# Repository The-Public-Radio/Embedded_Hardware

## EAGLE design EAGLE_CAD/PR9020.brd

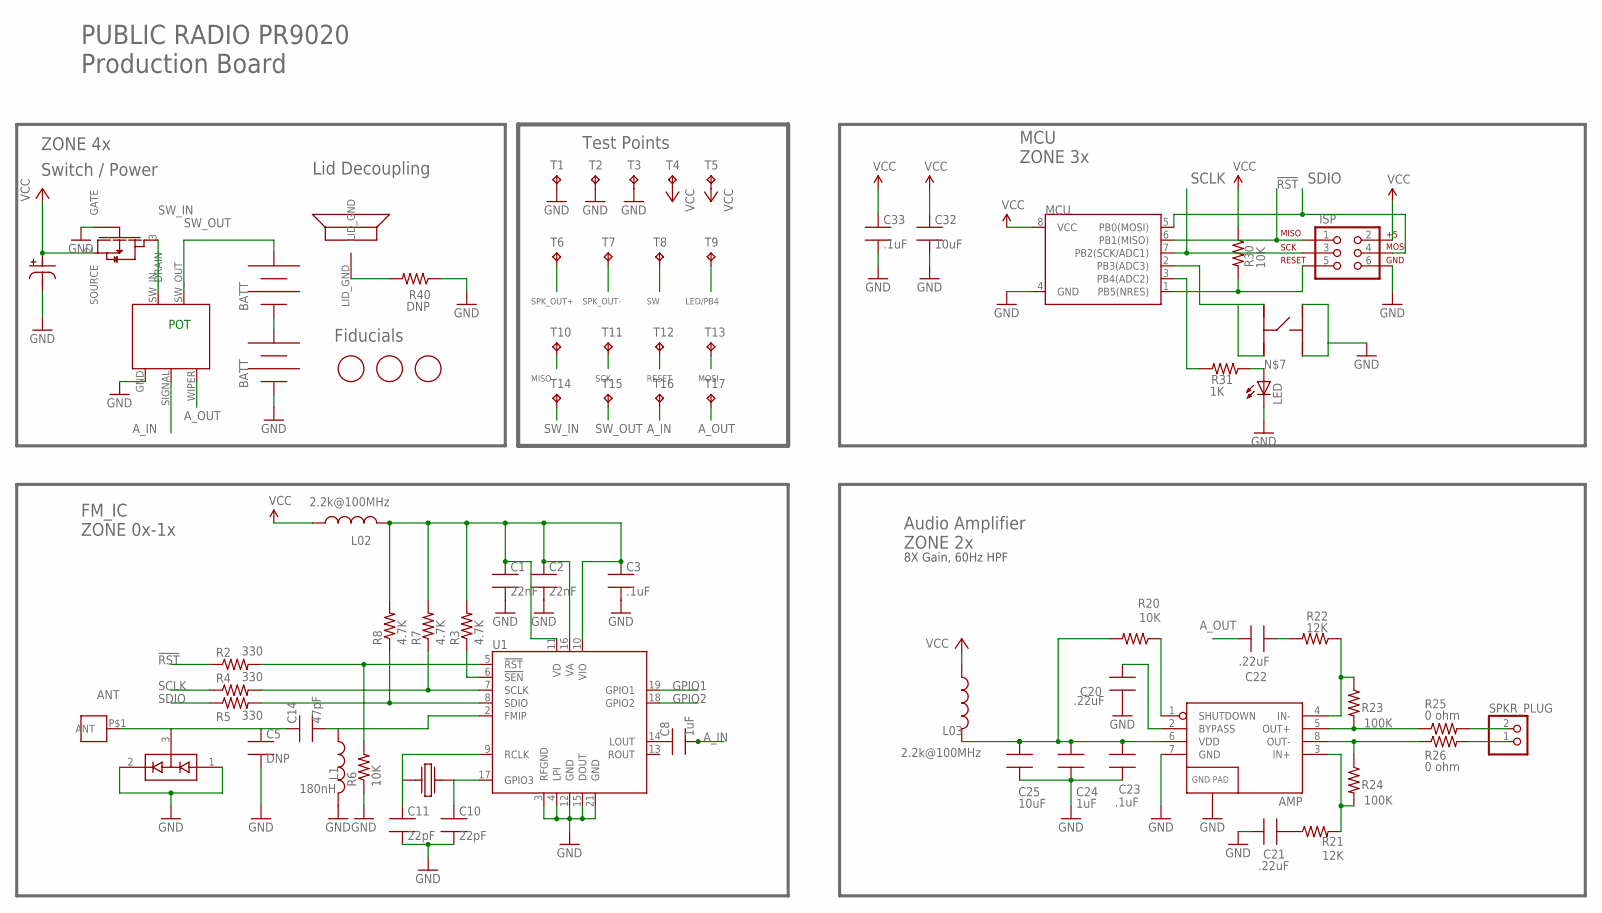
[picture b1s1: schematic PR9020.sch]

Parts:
AMP: TPA6203A1; 8-MSOP
ANT_MOUNT: DNP; M3_BOLT_HOLE
C1, C2: 22nF; 0603_CPL; VOLTAGE 16V; MFG_PN CL10B223KB8NNNC
C3, C23, C33: .1uF; 0603_CPL; VOLTAGE 16V; MFG_PN CL10B104KB8SFNC
C5: DNP; 0603_CPL; VOLTAGE 50V; MFG_PN DNP
C8, C24: 1uF; 0603_CPL; VOLTAGE 10V; MFG_PN CL10B105KP8NNNC
C10, C11: 22pF; 0603_CPL; VOLTAGE 50V; MFG_PN C1608C0G1H220J080AA
C14: 47pF; 0603_CPL; VOLTAGE 50V; MFG_PN CL10C470JB8NCNC
C20, C21, C22: .22uF; 0603_CPL; VOLTAGE 16V; MFG_PN C1608X7R1C224K080AC
C25, C32: 10uF; 0603_CPL; VOLTAGE 6.3V; MFG_PN CL10A106MQ8NNNC
C40: 220uF; NICHICON_UD_63; VOLTAGE 16V
D1: BAV99; SOT23_CPL; MFG_PN BAV99,215
FET1: AO3435; SOT23_CPL; MFG_PN AO3435
ISP: AVR_SPI_PRG_6NS; 2X3-NS
JP5, JP6: BK-92_MPD_AA_BATT_CLIP; BK92_AA_BATT; MFG_PN 2 of BK92 - supplied by CL Labs
L1: 180nH; 0805_ADAFRUIT; MFG_PN AISC-0805-R18J-T
L02, L03: 2.2k@100MHz; 0603_CPL; MFG_PN HZ0603A222R-10
LED: LEDCHIPLED_0805; CHIPLED_0805; MFG_PN LY R976-PS-36
MARK1, MARK2, MARK3: FIDUCIAL; FIDUCIAL_1MM
MCU: ATTINY45TINY45-20-SMT; 8-SOIC
R1: RV170SF_TAIWANA_POT_SW; RV170SF_SW_POT; MFG_PN RV170SF-43-20F-A10K - supplied by CL La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
R2, R4, R5: 330; 0603_CPL; MFG_PN MCR03ERTJ331
R3, R7, R8: 4.7K; 0603_CPL; MFG_PN ERJ-3EKF4701V
R6, R20, R30: 10K; 0603_CPL; MFG_PN ERJ-3GEYJ103V
R21, R22: 12K; 0603_CPL; MFG_PN RC0603FR-0712KL
R23, R24: 100K; 0603_CPL; MFG_PN ERJ-3EKF1003V
R25, R26: 0 ohm; 0805_ADAFRUIT; MFG_PN ERJ-6GEY0R00V
R31: 1K; 0603_CPL; MFG_PN ERJ-3EKF1001V
R40: DNP; 0603_CPL; MFG_PN ERJ-3GEY0R00V
SPKR_PLACE: DNP; PR2023_SPKR_PLACE
SPKR_PLUG: JST_2PIN-SMT-RA; JST-B2B-PH-SM4-TB
SW1: C&K_PTS645; C&K_PTS645_SMT
T1, T2, T3, T4, T5, T6, T7, T8, T9, T10, T11, T12, T13, T14, T15, T16, T17: TPTP20R; TP20R
U1: SI4702-C19-GMR; SI470X_20_QFN; MFG_PN Si4702 C19 GM - supplied by CL Labs
X1: ABS25XTAL; 4-SOJ

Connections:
3.3V: C1.1, C2.1, C3.1, L02.2, R3.2, R7.2, R8.2, U1.10 (VIO), U1.11 (VD), U1.16 (VA)
!RST: ISP.1, MCU.6 (PB1(MISO)), R2.1, T10.TP
!RST-L: R2.2, R6.2, U1.5 (!RST)
!SEN-L: R3.1, U1.6 (!SEN)
ANT: ANT_MOUNT.P$1, C5.1, C14.1, D1.3 (COM)
A_IN: C8.2, R1.SIGNAL, T16.TP
A_OUT: C22.2, R1.WIPER, T17.TP
GND: AMP.7 (GND), AMP.9 (GND), C1.2, C2.2, C3.2, C5.2, C10.2, C11.2, C20.1, C21.1, C23.2, C24.2, C25.2, C32.2, C33.2, C40.P$2, D1.1 (A1), D1.2 (C2), FET1.1 (GATE), ISP.6, JP6.NEG, JP6.NEG@2 (NEG), L1.2, LED.C, MCU.4 (GND), R1.GND, R6.1, R40.1, SW1.P$1, SW1.P$2, T1.TP, T2.TP, T3.TP, U1.3 (RFGND), U1.4 (LPI), U1.12 (GND), U1.15 (DOUT), U1.21 (GND)
GPIO1: U1.19 (GPIO1)
GPIO2: U1.18 (GPIO2)
LED/PB4: MCU.3 (PB4(ADC2)), R31.2, T9.TP
unnamed: C11.1, U1.9 (RCLK), X1.P$1
unnamed: AMP.6 (VDD), C23.1, C24.1, C25.1, L03.2, R20.2
unnamed: C22.1, R22.2
unnamed: AMP.5 (OUT+), R23.2, R25.1
unnamed: AMP.3 (IN+), R21.2, R24.2
unnamed: LED.A, R31.1
unnamed: R40.2, SPKR_PLACE.LID_GND
unnamed: C8.1, U1.14 (LOUT)
unnamed: C10.1, U1.17 (GPIO3), X1.P$4
unnamed: AMP.8 (OUT-), R24.1, R26.1
unnamed: AMP.2 (BYPASS), C20.2
unnamed: JP5.NEG, JP5.NEG@2 (NEG), JP6.POS, JP6.POS@2 (POS)
unnamed: AMP.4 (IN-), R22.1, R23.1
unnamed: C14.2, L1.1, U1.2 (FMIP)
unnamed: AMP.1 (SHUTDOWN), R20.1
unnamed: C21.2, R21.1
RESET: ISP.5, MCU.1 (PB5(NRES)), R30.2, T12.TP
SCLK: ISP.3, MCU.7 (PB2(SCK/ADC1)), R4.1, T11.TP
SCLK-L: R4.2, R7.1, U1.7 (SCLK)
SDIO: ISP.4, MCU.5 (PB0(MOSI)), R5.1, T13.TP
SDIO-L: R5.2, R8.1, U1.8 (SDIO)
SPK_OUT+: R25.2, SPKR_PLUG.2 (1), T6.TP
SPK_OUT-: R26.2, SPKR_PLUG.1 (2), T7.TP
SW: MCU.2 (PB3(ADC3)), SW1.P$3, SW1.P$4, T8.TP
SW_IN: FET1.3 (DRAIN), R1.SW_IN, T14.TP
SW_OUT: JP5.POS, JP5.POS@2 (POS), R1.SW_OUT, T15.TP
VCC: C32.1, C33.1, C40.P$1, FET1.2 (SOURCE), ISP.2, L02.1, L03.1, MCU.8 (VCC), R30.1, T4.TP, T5.TP

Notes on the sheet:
POT
FM_IC ZONE 0x-1x
Switch / Power
Lid Decoupling
Audio Amplifier ZONE 2x
MCU ZONE 3x
PUBLIC RADIO PR9020 Production Board
Fiducials
Test Points
MISO
SCK
RESET
MOSI
8X Gain, 60Hz HPF
ZONE 4x

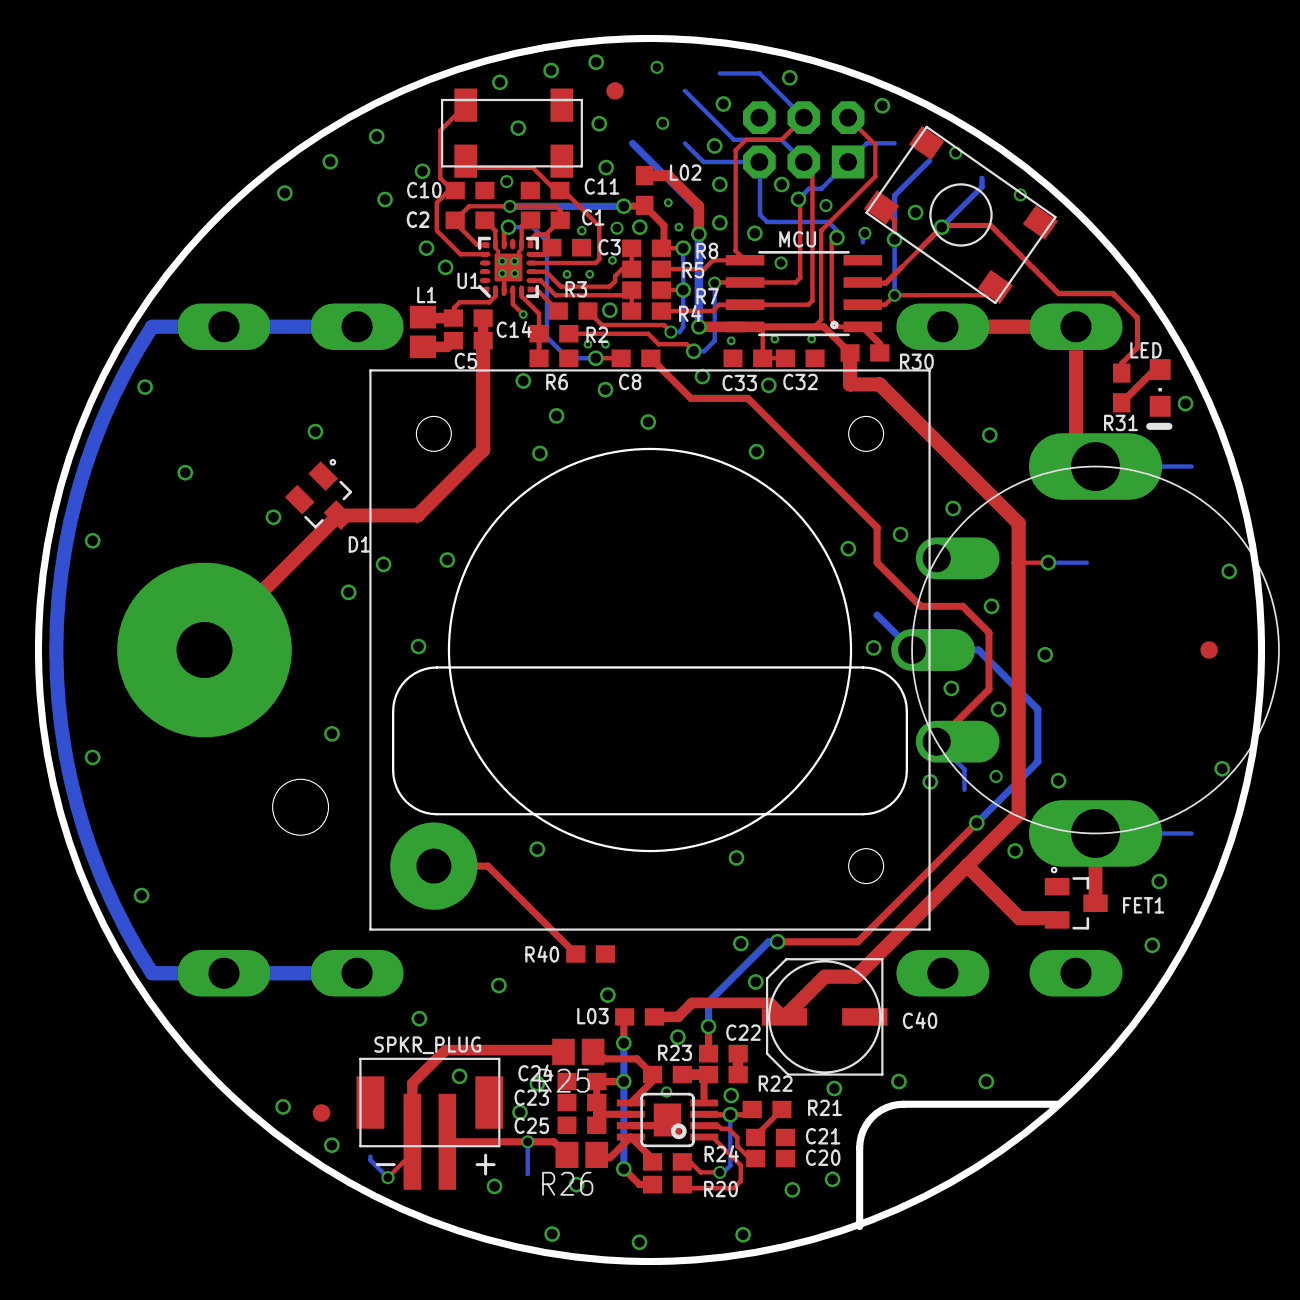
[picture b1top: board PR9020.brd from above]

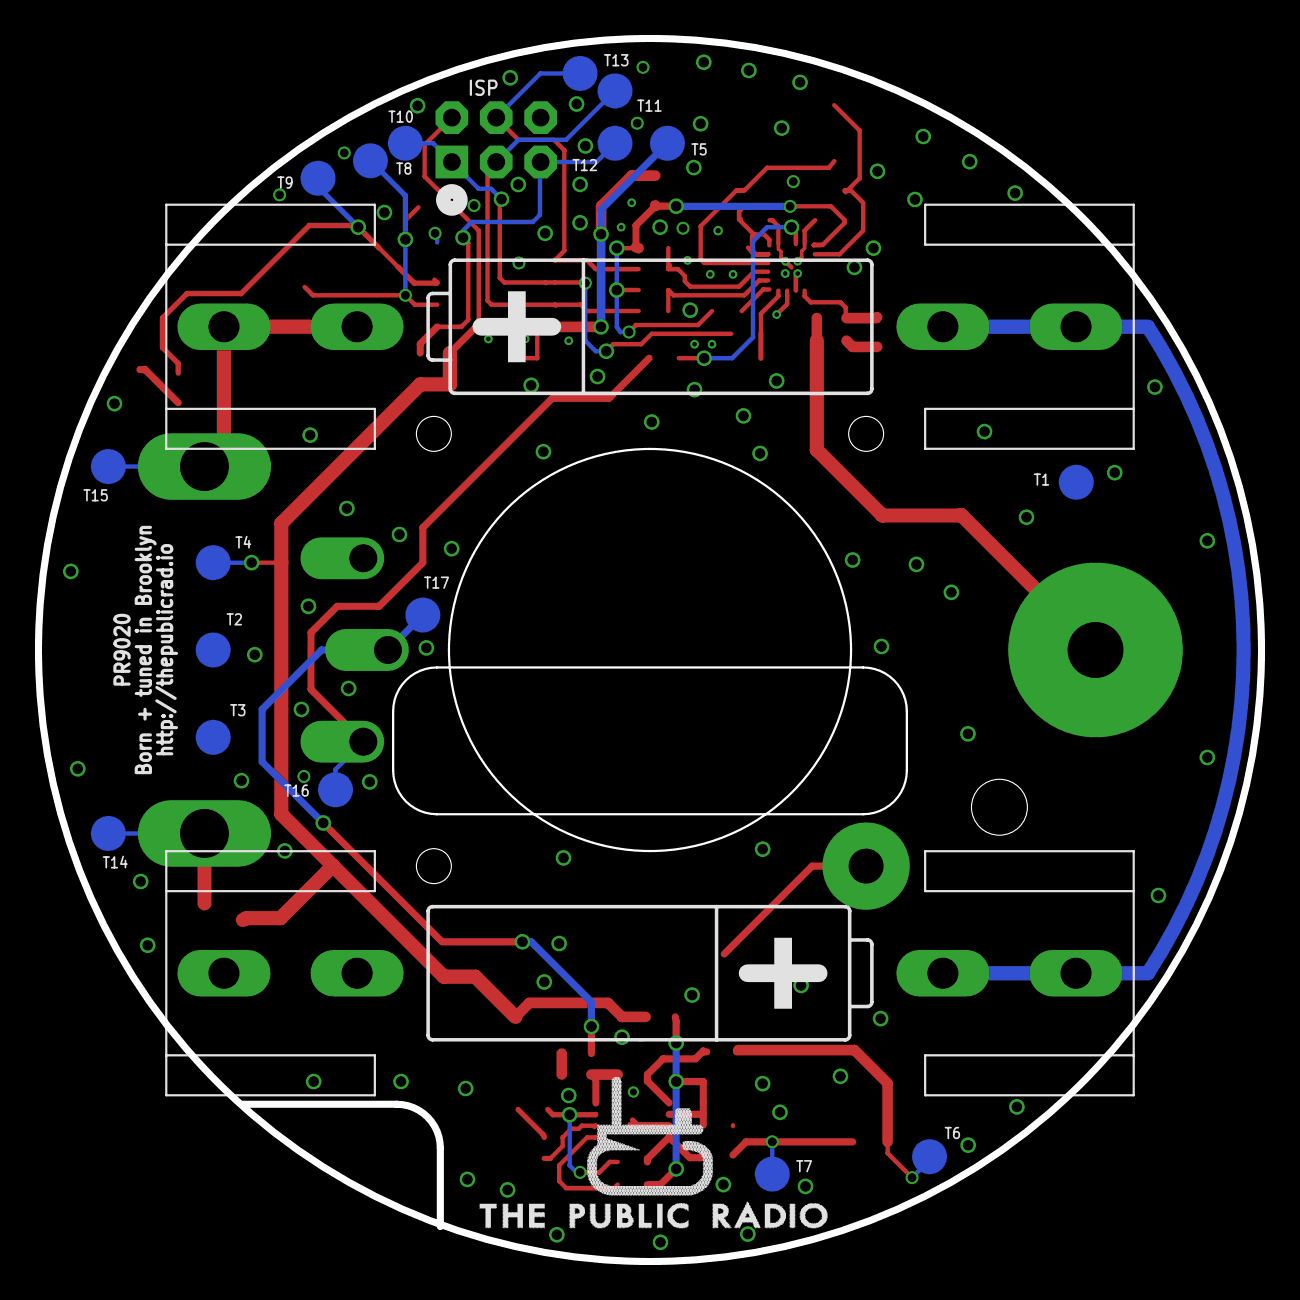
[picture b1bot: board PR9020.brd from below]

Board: 2 copper layers, 70.0 x 70.0 mm, 73 parts (21 on the bottom side), 36 nets.

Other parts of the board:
U$1: PR_LOGO

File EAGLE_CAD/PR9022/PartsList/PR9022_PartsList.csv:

Partlist

Exported from PR9022.brd at 9/28/15 9:47 PM

EAGLE Version 6.6.0 Copyright (c) 1988-2014 CadSoft

Assembly variant: 

Part       Value          Package           Library          Position (mm)         Orientation

AMP                       8-MSOP            PR_Parts_Library (34.1 10.2)           R0
ANT_MOUNT  DNP            PEM_M3            PR_Parts_Library (9.5 35)              R0
C1         22nF           0603_CPL          PR_Parts_Library (29.01 59.6)          R180
C2         22nF           0603_CPL          PR_Parts_Library (24.7 59.6)           R0
C3         .1uF           0603_CPL          PR_Parts_Library (30.24 58.03)         R0
C8         1uF            0603_CPL          PR_Parts_Library (34.2 51.7)           R0
C10        22pF           0603_CPL          PR_Parts_Library (24.7 61.3)           R0
C11        22pF           0603_CPL          PR_Parts_Library (29 61.3)             R180
C14        47pF           0603_CPL          PR_Parts_Library (24.7 54)             R180
C20        .22uF          0603_CPL          PR_Parts_Library (31.8 4)              R0
C21        .22uF          0603_CPL          PR_Parts_Library (35.5 2.2)            R0
C22        .22uF          0603_CPL          PR_Parts_Library (38.5 7)              R90
C23        .1uF           0603_CPL          PR_Parts_Library (34.5 15.1)           R90
C24        1uF            0603_CPL          PR_Parts_Library (36.5 15.1)           R90
C25        10uF           0603_CPL          PR_Parts_Library (32.5 15.1)           R90
C32        10uF           0603_CPL          PR_Parts_Library (42 52.3)             R270
C33        .1uF           0603_CPL          PR_Parts_Library (40.2 52.3)           R270
C40        220uF          NICHICON_UD_63    PR_Parts_Library (45.7 12.2)           R180
D1                        SOT23_CPL         PR_Parts_Library (16.4 43.5)           R315
FET1                      SOT23_CPL         PR_Parts_Library (59.4 20.5)           R0
ISP                       2X3-NS            PR_Parts_Library (43.8 64.2)           MR0
JP5                       BK92_AA_BATT      PR_Parts_Library (35 53.5)             MR180
JP6                       BK92_AA_BATT      PR_Parts_Library (35 16.5)             MR0
L1         180nH          0805_ADAFRUIT     PR_Parts_Library (22 53.2)             R270
L02        2.2k@100MHz    0603_CPL          PR_Parts_Library (34.7 61.3)           R270
L03        2.2k@100MHz    0603_CPL          PR_Parts_Library (40 11.8)             R90
LED                       CHIPLED_0805      adafruit         (64.2 50)             R180
MARK1                     FIDUCIAL_1MM      PR_Parts_Library (16.2 8.5)            R0
MARK2                     FIDUCIAL_1MM      PR_Parts_Library (33 67)               R0
MARK3                     FIDUCIAL_1MM      PR_Parts_Library (67 35)               R0
MCU                       8-SOIC            PR_Parts_Library (43.7 56.4)           R90
R1                        RV170SF_SW_POT    PR_Parts_Library (60.5 35)             R270
R2         330            0603_CPL          PR_Parts_Library (29.5 53.1)           R180
R3         4.7K           0603_CPL          PR_Parts_Library (30.6 54.4)           R0
R4         330            0603_CPL          PR_Parts_Library (34.8 54.4)           R180
R5         330            0603_CPL          PR_Parts_Library (34.8 56.8)           R180
R6         10K            0603_CPL          PR_Parts_Library (29.5 51.7)           R180
R7         4.7K           0603_CPL          PR_Parts_Library (34.8 55.6)           R0
R8         4.7K           0603_CPL          PR_Parts_Library (34.8 58)             R0
R20        10K            0603_CPL          PR_Parts_Library (29.9 10.2)           R90
R21        12K            0603_CPL          PR_Parts_Library (35.5 4)              R180
R22        12K            0603_CPL          PR_Parts_Library (36.7 7)              R270
R23        100K           0603_CPL          PR_Parts_Library (36.7 10.2)           R90
R24        100K           0603_CPL          PR_Parts_Library (31.7 10.2)           R270
R25        0 ohm          0805_ADAFRUIT     PR_Parts_Library (38.6 15.1)           R90
R26        0 ohm          0805_ADAFRUIT     PR_Parts_Library (30.4 15.1)           R90
R30        10K            0603_CPL          PR_Parts_Library (45.4 53)             R0
R31        1K             0603_CPL          PR_Parts_Library (62 50)               R90
R40        DNP            0603_CPL          PR_Parts_Library (24.2 15.3)           R90
SPKR_PLACE DNP            PR2024_SPKR_PLACE PR_Parts_Library (35 35)               R0
SW1                       C&K_PTS645_SMT    PR_Parts_Library (52.8 59.9)           R325
T1                        TP20R             PR_Parts_Library (10.6 44.6)           MR0
T2                        TP20R             PR_Parts_Library (60 35)               MR0
T3                        TP20R             PR_Parts_Library (60 30)               MR0
T4                        TP20R             PR_Parts_Library (60 40)               MR0
T5                        TP20R             PR_Parts_Library (34 64)               MR0
T6                        TP20R             PR_Parts_Library (37 21)               MR0
T7                        TP20R             PR_Parts_Library (32 21)               MR0
T8                        TP20R             PR_Parts_Library (51 63)               MR0
T9                        TP20R             PR_Parts_Library (54 62)               MR0
T10                       TP20R             PR_Parts_Library (49 64)               MR0
T11                       TP20R             PR_Parts_Library (37 67)               MR0
T12                       TP20R             PR_Parts_Library (37 64)               MR0
T13                       TP20R             PR_Parts_Library (39 68)               MR0
T14                       TP20R             PR_Parts_Library (66 24.5)             MR0
T15                       TP20R             PR_Parts_Library (66 45.5)             MR0
T16                       TP20R             PR_Parts_Library (53 27)               MR0
T17                       TP20R             PR_Parts_Library (48 37)               MR0
U1                        SI470X_20_QFN     PR_Parts_Library (26.9 56.9)           R90
X1                        4-SOJ             PR_Parts_Library (27.2 64.58)          R0

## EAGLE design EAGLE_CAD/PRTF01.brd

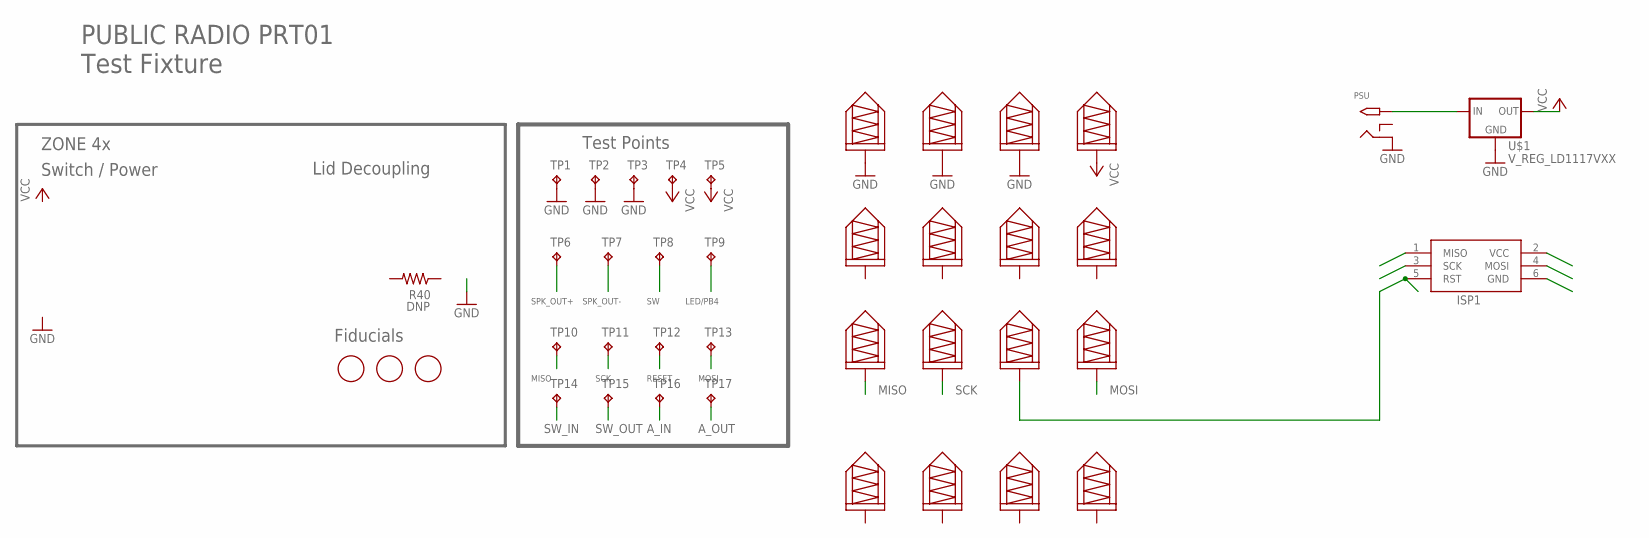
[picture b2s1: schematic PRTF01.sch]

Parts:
ISP1: AVRISP-6; AVRISP
MARK1, MARK2, MARK3: FIDUCIAL; FIDUCIAL_1MM
P1, P2, P3, P4, P6, P8, P9, P10, P11, P12, P13, P14, P15, P16, P17: 0908MILL_MAX_SPRINGPIN
PSU: 2.1MMJACKTHM; PJ-102A
R40: DNP; 0603_CPL; MFG_PN ERJ-3GEY0R00V
TP1, TP2, TP3, TP4, TP5, TP6, TP7, TP8, TP9, TP10, TP11, TP12, TP13, TP14, TP15, TP16, TP17: TPTP20R; TP20R
U$1: V_REG_LD1117VXX; 78XXL
U$P7: 0908MILL_MAX_SPRINGPIN

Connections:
!RST: TP10.TP
A_IN: TP16.TP
A_OUT: TP17.TP
GND: P1.P$1, P2.P$1, P3.P$1, PSU.RING, TP1.TP, TP2.TP, TP3.TP, U$1.IN (GND)
LED/PB4: TP9.TP
MISO: ISP1.1 (MISO), P10.P$1
MOSI: ISP1.4 (MOSI), P13.P$1
unnamed: PSU.TIP, U$1.OUT (IN)
RESET: ISP1.5 (RST), P12.P$1, TP12.TP
SCK: ISP1.3 (SCK), P11.P$1
SCLK: TP11.TP
SDIO: TP13.TP
SPK_OUT+: TP6.TP
SPK_OUT-: TP7.TP
SW: TP8.TP
SW_IN: TP14.TP
SW_OUT: TP15.TP
VCC: P4.P$1, TP4.TP, TP5.TP, U$1.GND (OUT)

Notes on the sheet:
Switch / Power
Lid Decoupling
PUBLIC RADIO PRT01 Test Fixture
Fiducials
Test Points
MISO
SCK
RESET
MOSI
ZONE 4x

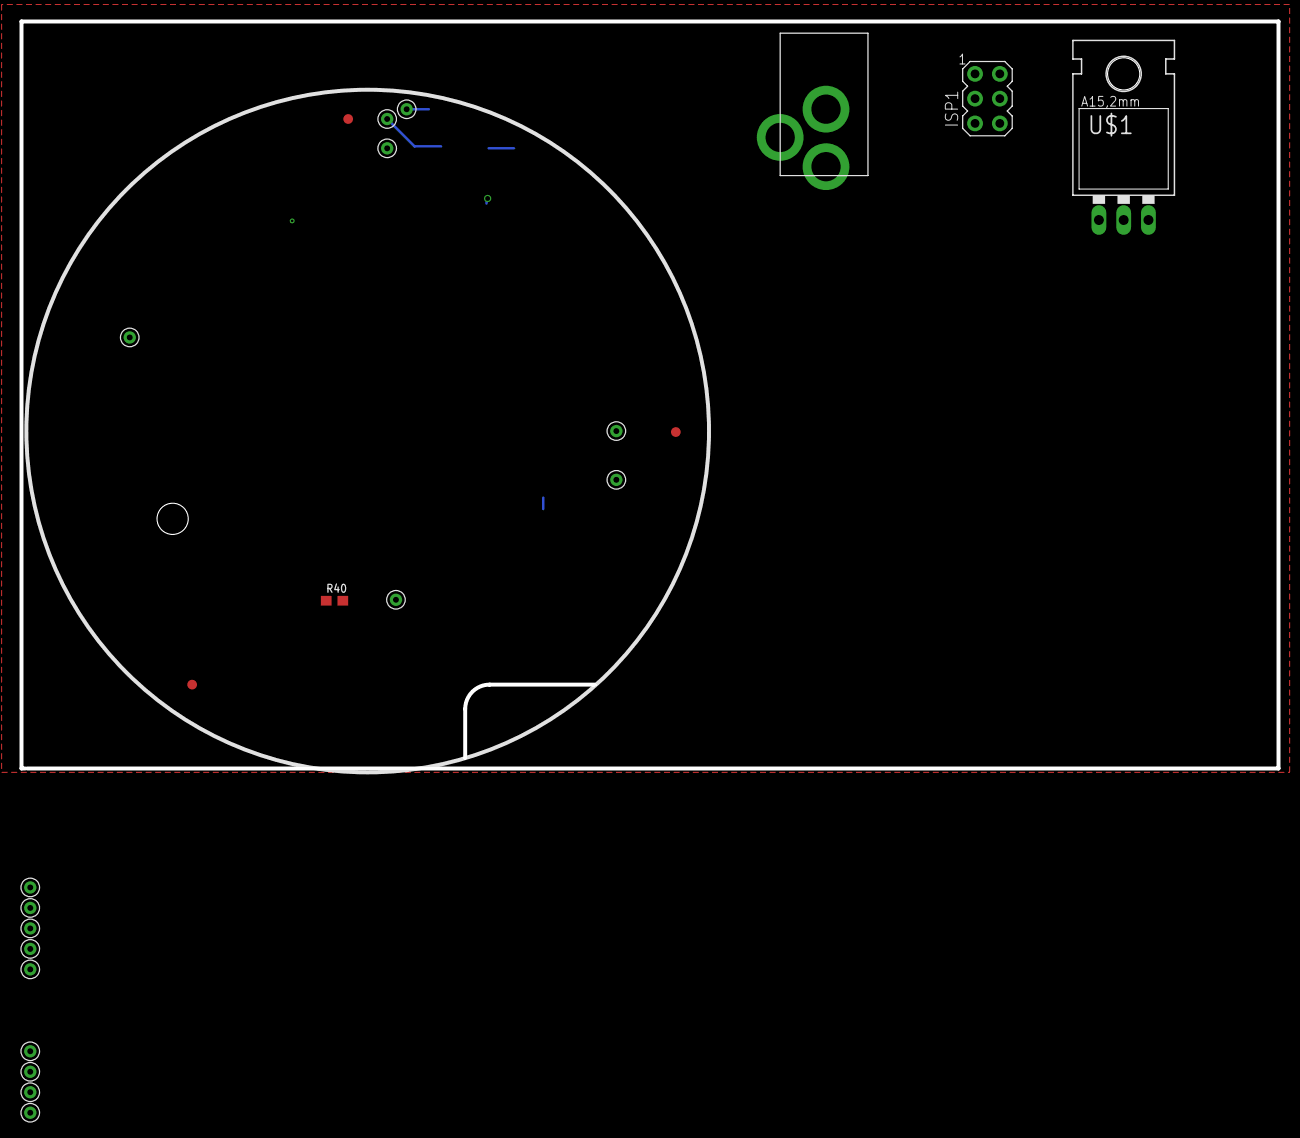
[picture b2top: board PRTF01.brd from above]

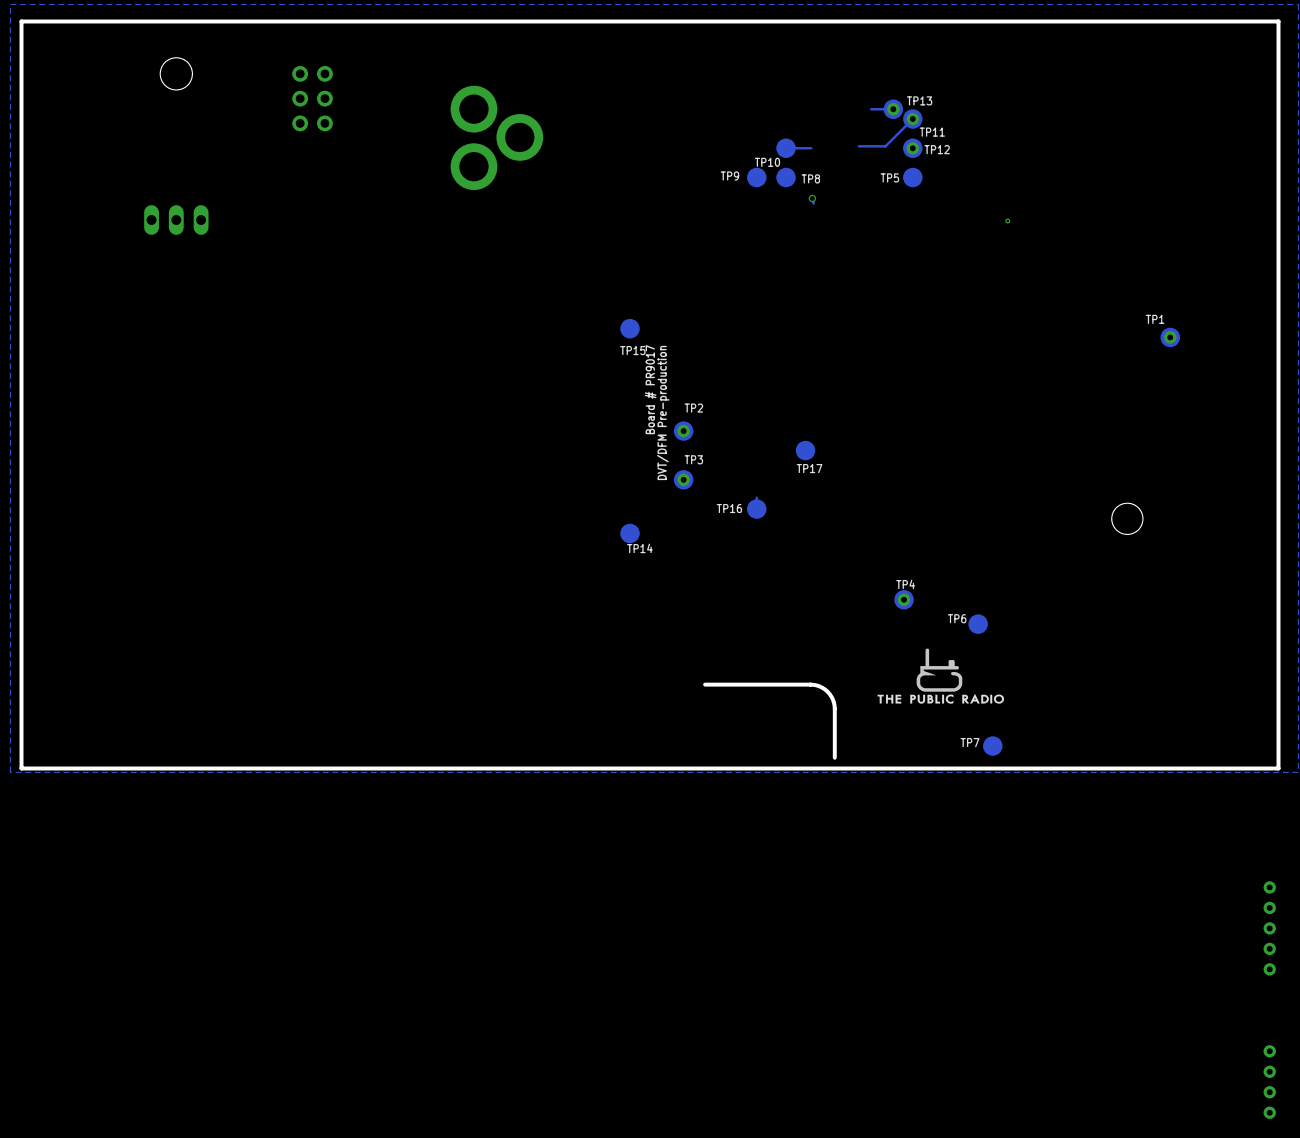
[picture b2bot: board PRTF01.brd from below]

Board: 2 copper layers, 128.9 x 76.6 mm, 40 parts (17 on the bottom side), 7 nets.

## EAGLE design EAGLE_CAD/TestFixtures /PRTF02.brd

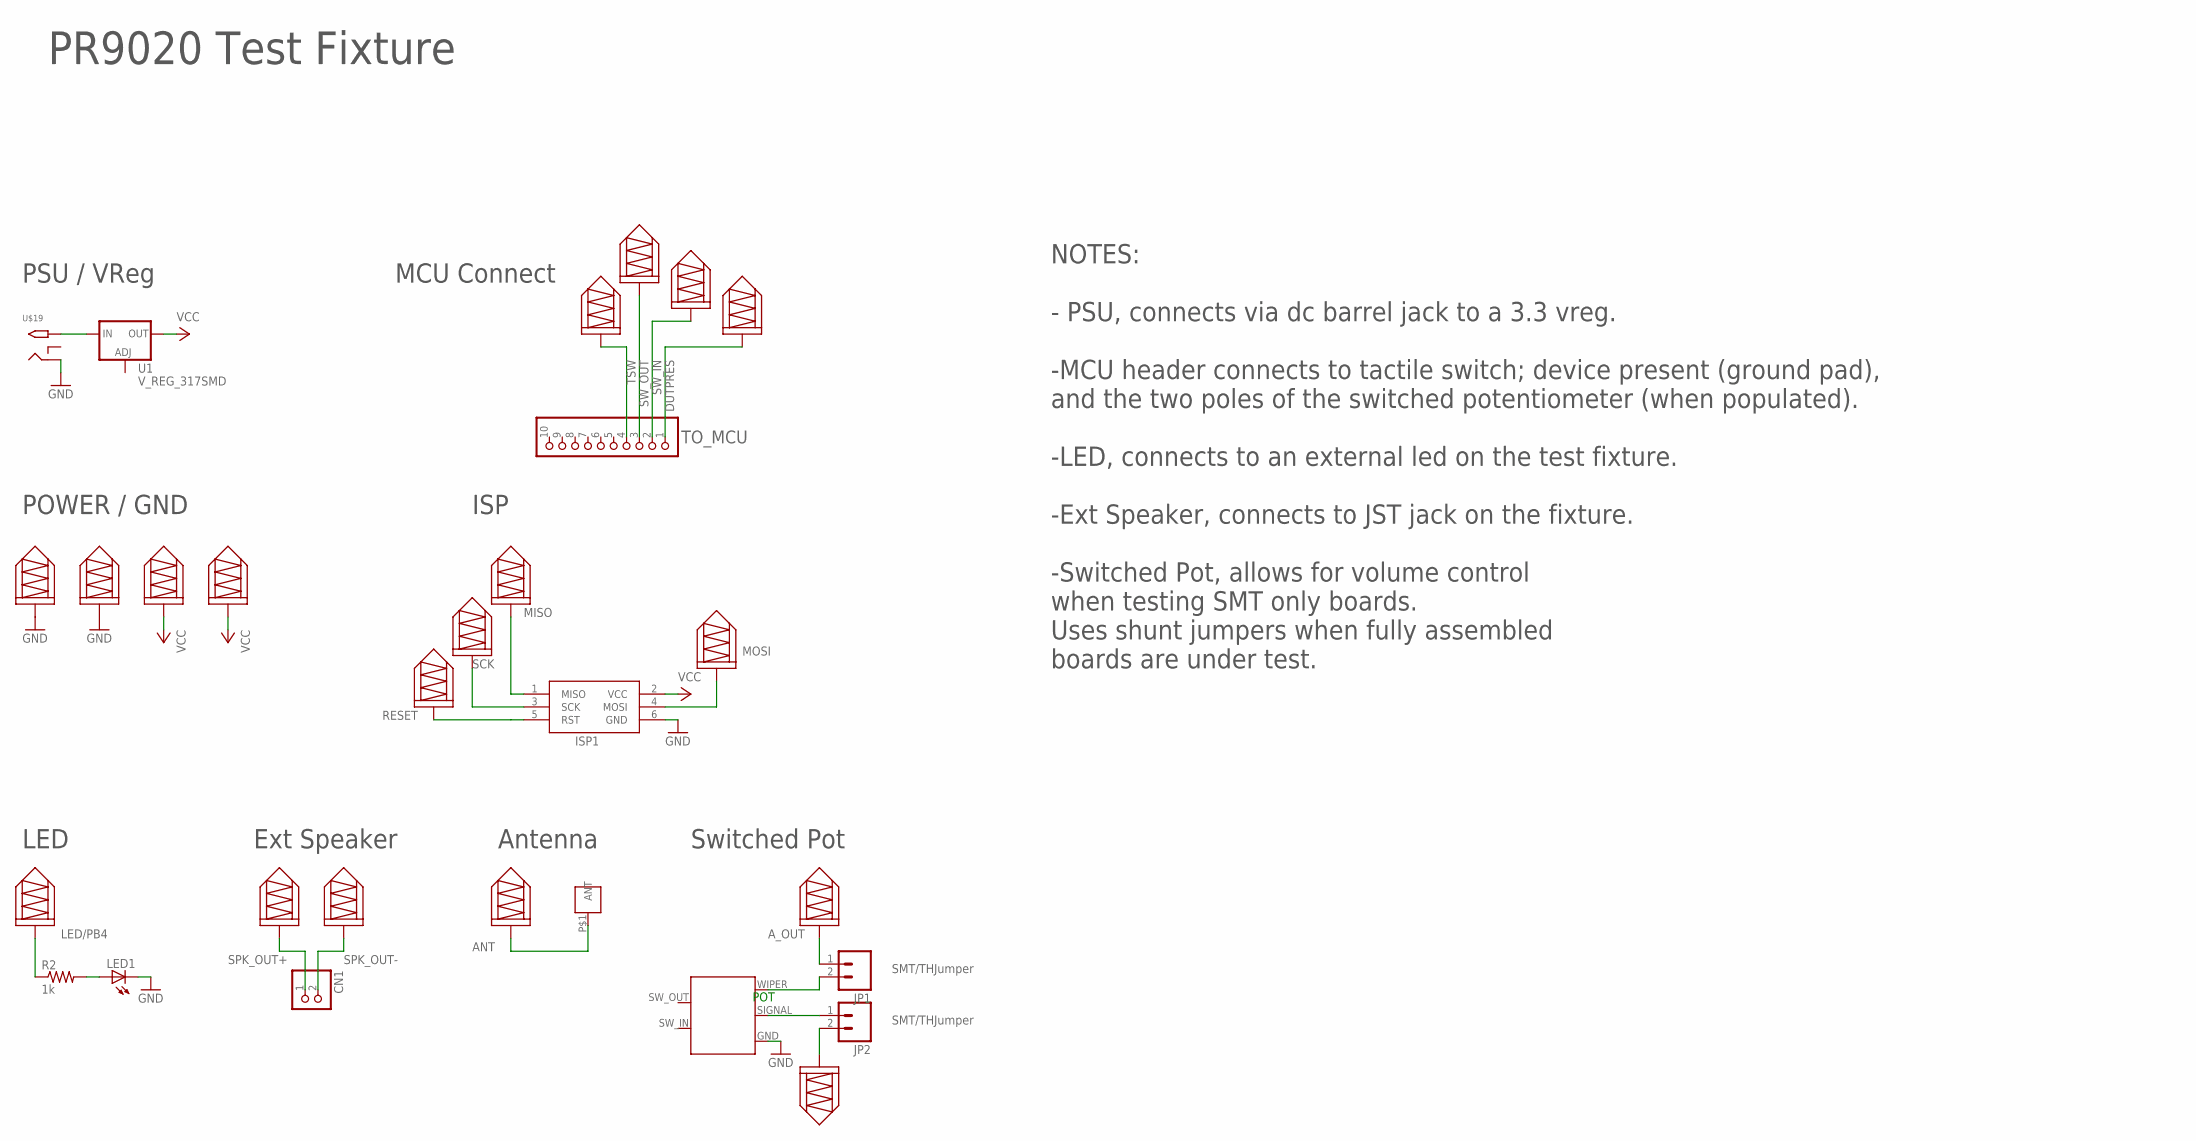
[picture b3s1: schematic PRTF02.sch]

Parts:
CN1: JST_2PIN-SMT-RA; JST-B2B-PH-SM4-TB
ISP1: AVRISP-6; AVRISP
J1: M3_SCREW_POST; M3_BOLT_HOLE
JP1, JP2: SMT/THJumper; 1X02_LOCK_LONGPADS
LED1: LED5MM
R1: RV170SF_TAIWANA_POT_SW; RV170SF_SW_POT; MFG_PN RV170SF-43-20F-A10K - supplied by CL La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
R2: 1k; 0805_ADAFRUIT
TO_MCU: PINHD-1X10; 1X10-BIG
U1: V_REG_317SMD; SOT223
U$2, U$3, U$4, U$5, U$6, U$7, U$8, U$9, U$10, U$11, U$12, U$13, U$14, U$15, U$16, U$17, U$18, U$21: 0908MILL_MAX_SPRINGPIN
U$19: 2.1MMJACKTHM; PJ-102A

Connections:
ANT: J1.P$1, U$21.P$1
A_OUT: JP1.1, U$18.P$1
DUTPRES: TO_MCU.1, U$2.P$1
GND: ISP1.6 (GND), LED1.K (C), R1.GND, U$3.P$1, U$4.P$1, U$19.RING
LED/PB4: R2.1, U$10.P$1
MISO: ISP1.1 (MISO), U$11.P$1
MOSI: ISP1.4 (MOSI), U$14.P$1
unnamed: U1.3 (IN), U$19.TIP
unnamed: LED1.A, R2.2
unnamed: JP2.1, R1.SIGNAL
unnamed: JP1.2, R1.WIPER
unnamed: JP2.2, U$17.P$1
RESET: U$13.P$1
RST: ISP1.5 (RST)
SCK: ISP1.3 (SCK), U$12.P$1
SPK_OUT+: CN1.1 (2), U$7.P$1
SPK_OUT-: CN1.2 (1), U$8.P$1
SW_IN: TO_MCU.2, U$15.P$1
SW_OUT: TO_MCU.3, U$16.P$1
TSW: TO_MCU.4, U$9.P$1
VCC: ISP1.2 (VCC), U1.2 (OUT), U$5.P$1, U$6.P$1

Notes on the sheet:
POT
POWER / GND
Switched Pot
Antenna
Ext Speaker
LED
ISP
PSU / VReg
MCU Connect
NOTES: - PSU, connects via dc barrel jack to a 3.3 vreg. -MCU header connects to tactile switch; device present (ground pad), and the two poles of the switched potentiometer (when populated). -LED, connects to an external led on the test fixture. -Ext Speaker, connects to JST jack on the fixture. -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
PR9020 Test Fixture

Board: 2 copper layers, 30 parts (0 on the bottom side), 19 nets, no tracks yet.

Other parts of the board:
U$1: PR_LOGO

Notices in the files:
parts and their libraries:
SparkFun-Aesthetics: Licensing: CC v3.0 Share-Alike You are welcome to use this library for commercial purposes.
SparkFun-PowerIC: Licensing: Creative Commons ShareAlike 4.0 International - https://creativecommons.org/licenses/by-sa/4.0
